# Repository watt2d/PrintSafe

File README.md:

# PrintSafe
3D filament dehumidifier based on the ESP32

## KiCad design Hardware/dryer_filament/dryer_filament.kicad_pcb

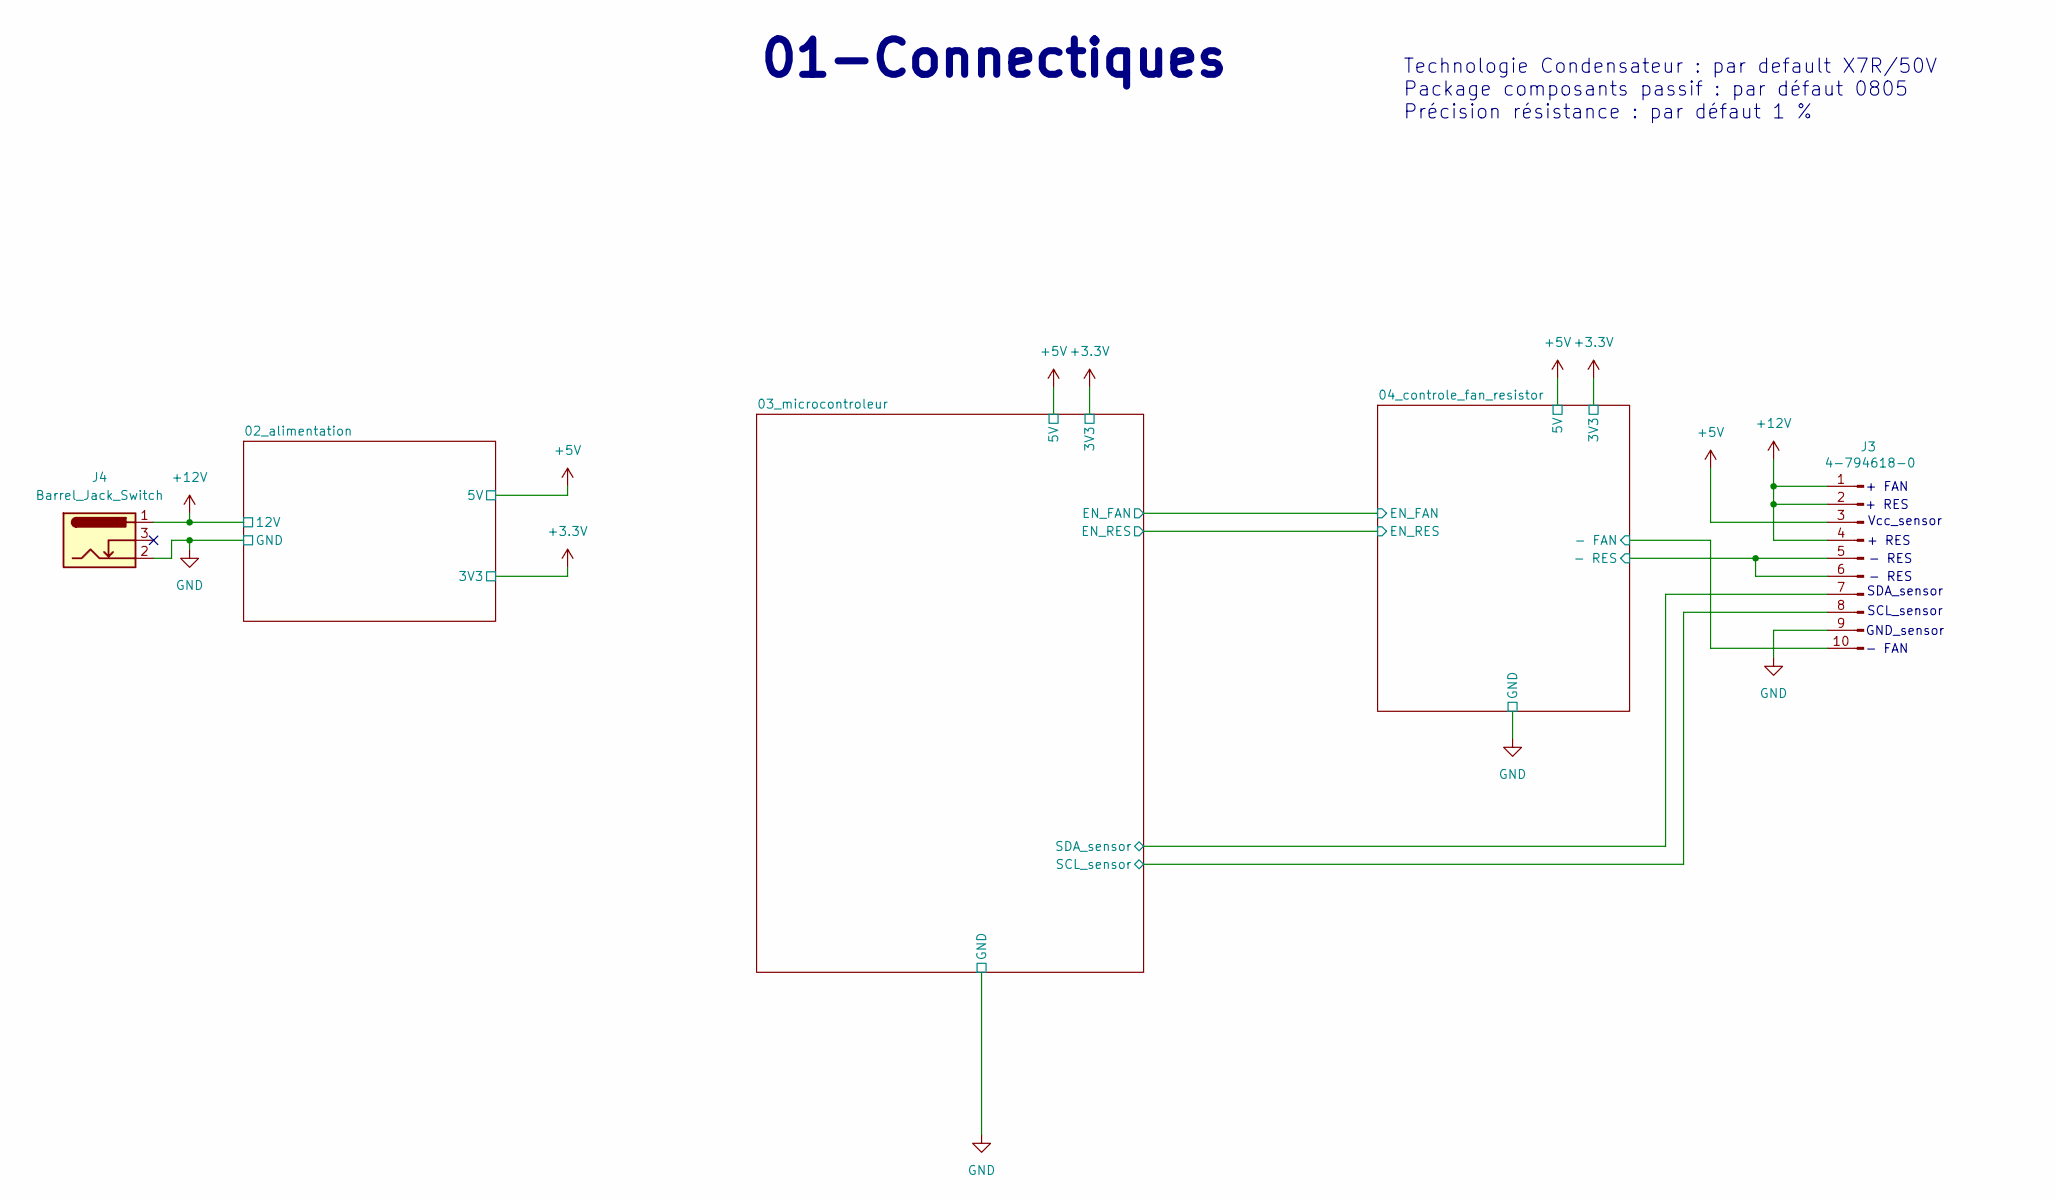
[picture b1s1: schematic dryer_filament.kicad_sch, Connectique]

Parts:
J3: 4-794618-0; 47946180
J4: Barrel_Jack_Switch; BarrelJack_CUI_PJ-102AH_Horizontal

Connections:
+5V: J3.3; also elsewhere on the board
+12V: J3.1, J3.2, J3.4, J4.1; also elsewhere on the board
/03_microcontroleur/SCL_sensor: J3.8; also elsewhere on the board
/03_microcontroleur/SDA_sensor: J3.7; also elsewhere on the board
/04_controle_fan_resistor/- FAN: J3.10; also elsewhere on the board
/04_controle_fan_resistor/- RES: J3.5, J3.6; also elsewhere on the board
GND: J3.9, J4.2; also elsewhere on the board

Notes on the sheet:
Vcc_sensor
SCL_sensor
- RES
+ RES
- FAN
+ FAN
GND_sensor
Technologie Condensateur : par default X7R/50V Package composants passif : par défaut 0805 Précision résistance : par défaut 1 %
01-Connectiques
SDA_sensor

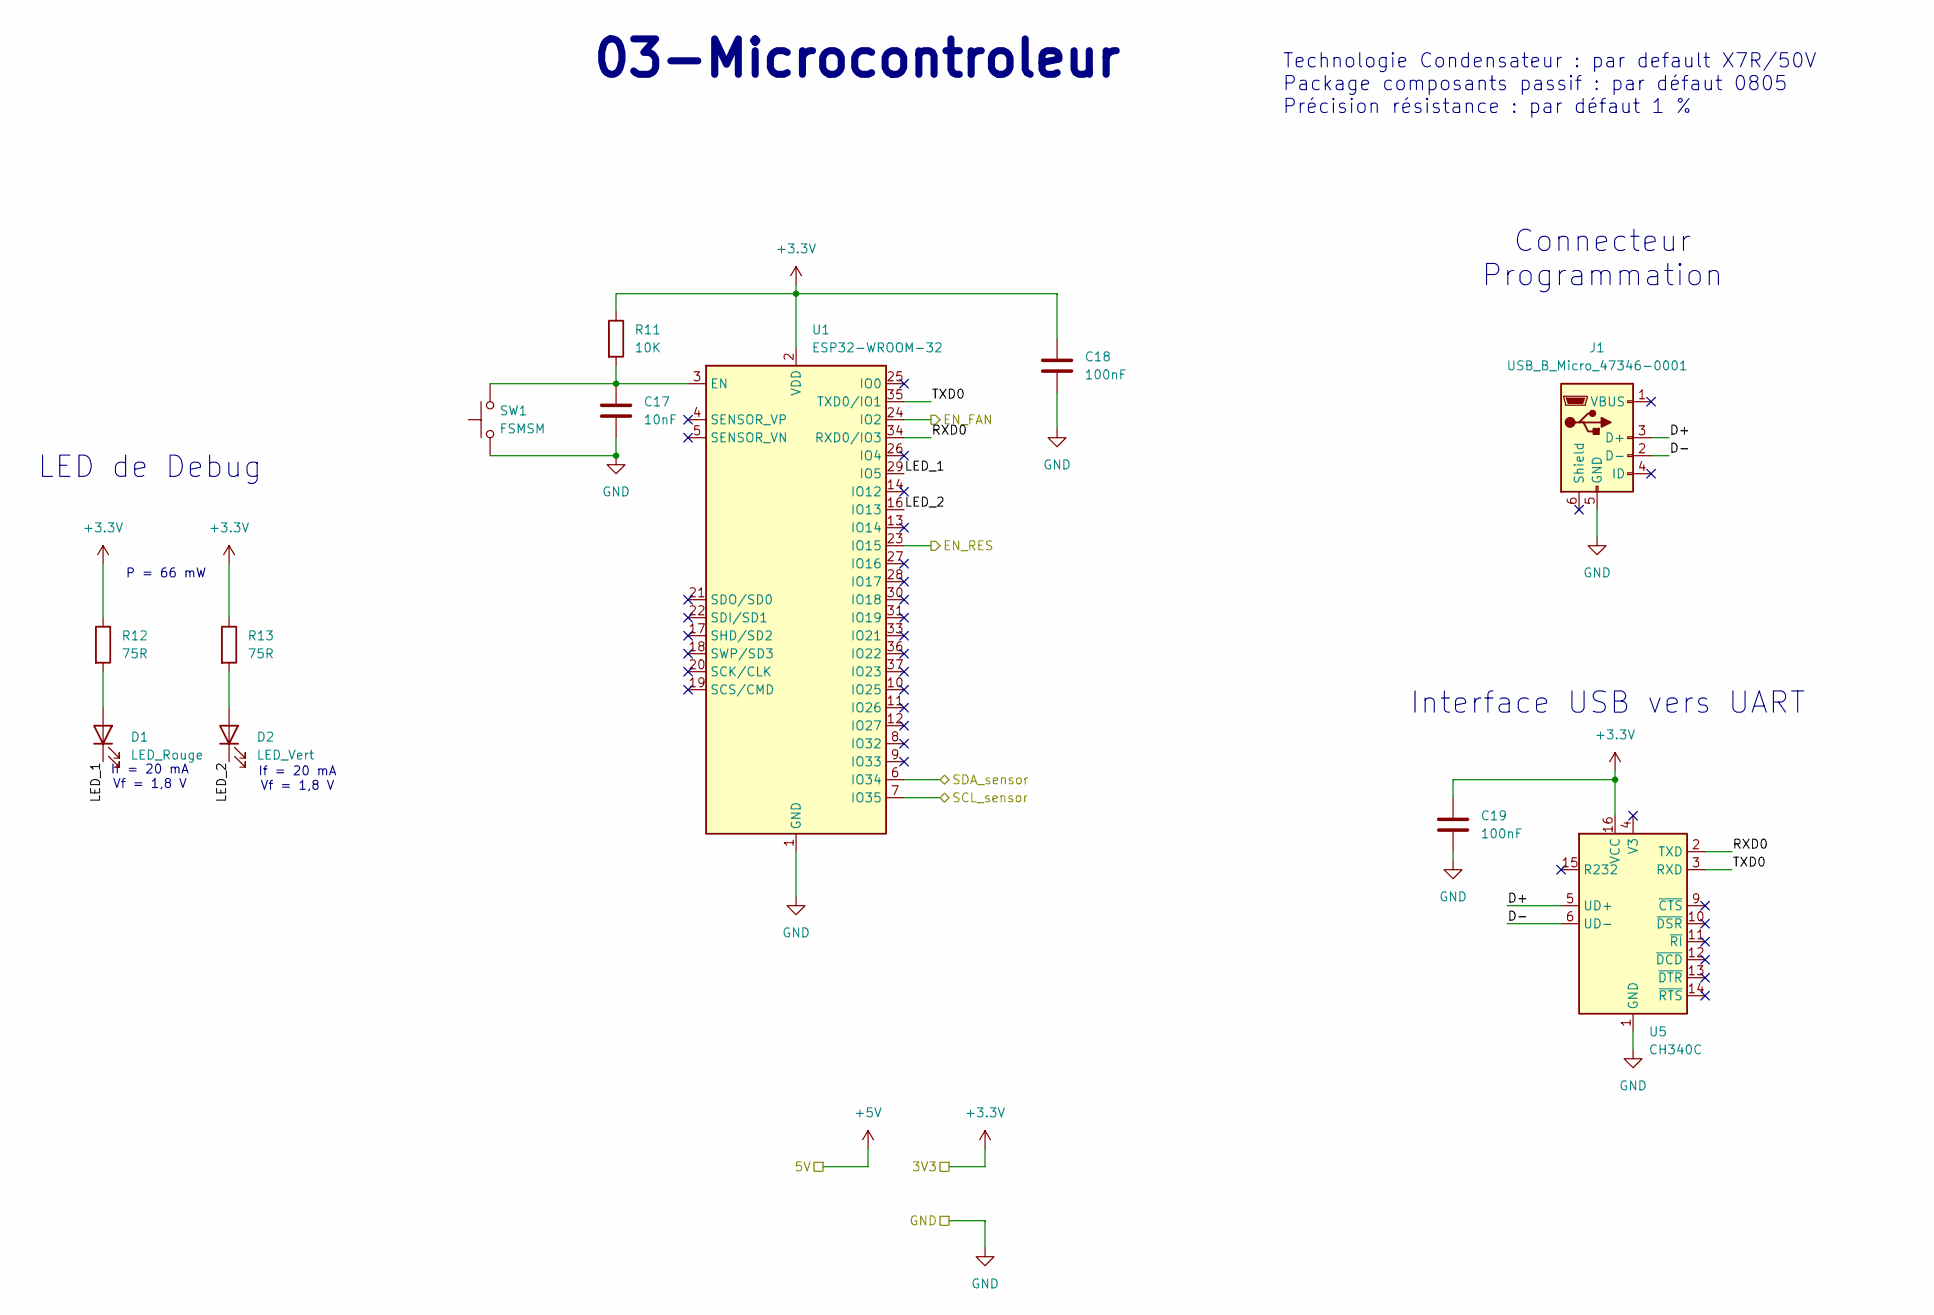
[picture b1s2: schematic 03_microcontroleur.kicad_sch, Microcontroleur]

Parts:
C17: 10nF; C_0805_2012Metric_Pad1.18x1.45mm_HandSolder
C18, C19: 100nF; C_0805_2012Metric_Pad1.18x1.45mm_HandSolder
D1: LED_Rouge; D_0805_2012Metric_Pad1.15x1.40mm_HandSolder
D2: LED_Vert; D_0805_2012Metric_Pad1.15x1.40mm_HandSolder
J1: USB_B_Micro_47346-0001; USB_Micro-B_Molex_47346-0001
R11: 10K; R_0805_2012Metric_Pad1.20x1.40mm_HandSolder
R12, R13: 75R; R_0805_2012Metric_Pad1.20x1.40mm_HandSolder
SW1: FSMSM; SW_Tactile_SPST_NO_Straight_CK_PTS636Sx25SMTRLFS
U1: ESP32-WROOM-32
U5: CH340C; SOIC-16_3.9x9.9mm_P1.27mm

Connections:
+3.3V: C18.1, C19.1, R11.1, R12.1, R13.1, U1.2 (VDD), U5.16 (VCC); also elsewhere on the board
/03_microcontroleur/D+: J1.3 (D+), U5.5 (UD+)
/03_microcontroleur/D-: J1.2 (D-), U5.6 (UD-)
/03_microcontroleur/EN_FAN: U1.24 (IO2); also elsewhere on the board
/03_microcontroleur/EN_RES: U1.23 (IO15); also elsewhere on the board
/03_microcontroleur/LED_1: D1.1 (K), U1.29 (IO5)
/03_microcontroleur/LED_2: D2.1 (K), U1.16 (IO13)
/03_microcontroleur/RXD0: U1.34 (RXD0/IO3), U5.2 (TXD)
/03_microcontroleur/SCL_sensor: U1.7 (IO35); also elsewhere on the board
/03_microcontroleur/SDA_sensor: U1.6 (IO34); also elsewhere on the board
/03_microcontroleur/TXD0: U1.35 (TXD0/IO1), U5.3 (RXD)
GND: C17.2, C18.2, C19.2, J1.5 (GND), SW1.1, U1.1 (GND), U1.15 (GND), U1.38 (GND), U1.39 (GND), U5.1 (GND); also elsewhere on the board
unnamed: D1.2 (A), R12.2
unnamed: D2.2 (A), R13.2
unnamed: C17.1, R11.2, SW1.2, U1.3 (EN)

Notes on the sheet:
Interface USB vers UART
If = 20 mA Vf = 1,8 V
Technologie Condensateur : par default X7R/50V Package composants passif : par défaut 0805 Précision résistance : par défaut 1 %
P = 66 mW
Connecteur Programmation
03-Microcontroleur
LED de Debug

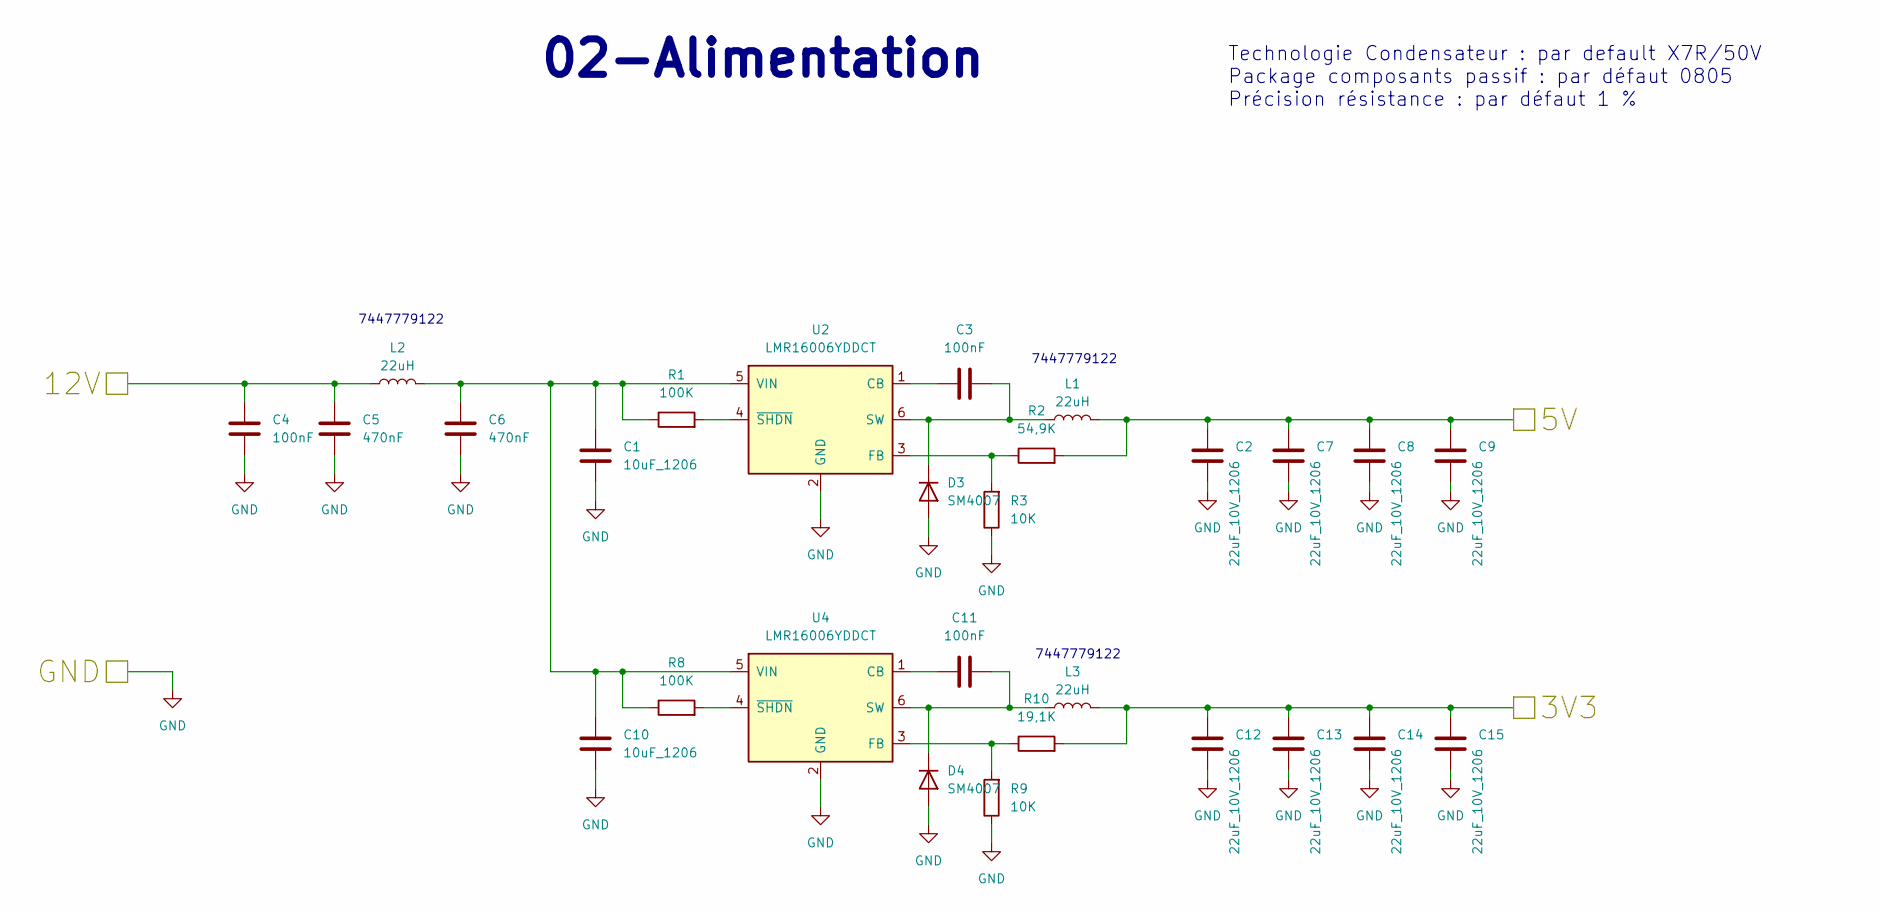
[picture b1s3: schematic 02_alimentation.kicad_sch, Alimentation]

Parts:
C1, C10: 10uF_1206; C_1206_3216Metric_Pad1.33x1.80mm_HandSolder
C2, C7, C8, C9, C12, C13, C14, C15: 22uF_10V_1206; C_1206_3216Metric_Pad1.33x1.80mm_HandSolder
C3, C4, C11: 100nF; C_0805_2012Metric_Pad1.18x1.45mm_HandSolder
C5, C6: 470nF; C_0805_2012Metric_Pad1.18x1.45mm_HandSolder
D3, D4: SM4007; D_SOD-123
L1, L2, L3: 22uH; L_Wuerth_WE-PD-Typ-M-Typ-S
R1, R8: 100K; R_0805_2012Metric_Pad1.20x1.40mm_HandSolder
R2: 54,9K; R_0805_2012Metric_Pad1.20x1.40mm_HandSolder
R3, R9: 10K; R_0805_2012Metric_Pad1.20x1.40mm_HandSolder
R10: 19,1K; R_0805_2012Metric_Pad1.20x1.40mm_HandSolder
U2, U4: LMR16006YDDCT; SOT-23-6

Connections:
+3.3V: C12.1, C13.1, C14.1, C15.1, L3.2, R10.2; also elsewhere on the board
+5V: C2.1, C7.1, C8.1, C9.1, L1.2, R2.2; also elsewhere on the board
+12V: C4.1, C5.1, L2.1; also elsewhere on the board
GND: C1.2, C2.2, C4.2, C5.2, C6.2, C7.2, C8.2, C9.2, C10.2, C12.2, C13.2, C14.2, C15.2, D3.2 (A), D4.2 (A), R3.1, R9.1, U2.2 (GND), U4.2 (GND); also elsewhere on the board
unnamed: C3.2, D3.1 (K), L1.1, U2.6 (SW)
unnamed: C11.2, D4.1 (K), L3.1, U4.6 (SW)
unnamed: C3.1, U2.1 (CB)
unnamed: R2.1, R3.2, U2.3 (FB)
unnamed: C1.1, C6.1, C10.1, L2.2, R1.1, R8.1, U2.5 (VIN), U4.5 (VIN)
unnamed: R1.2, U2.4 (~SHDN)
unnamed: C11.1, U4.1 (CB)
unnamed: R9.2, R10.1, U4.3 (FB)
unnamed: R8.2, U4.4 (~SHDN)

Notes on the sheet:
7447779122
Technologie Condensateur : par default X7R/50V Package composants passif : par défaut 0805 Précision résistance : par défaut 1 %
02-Alimentation

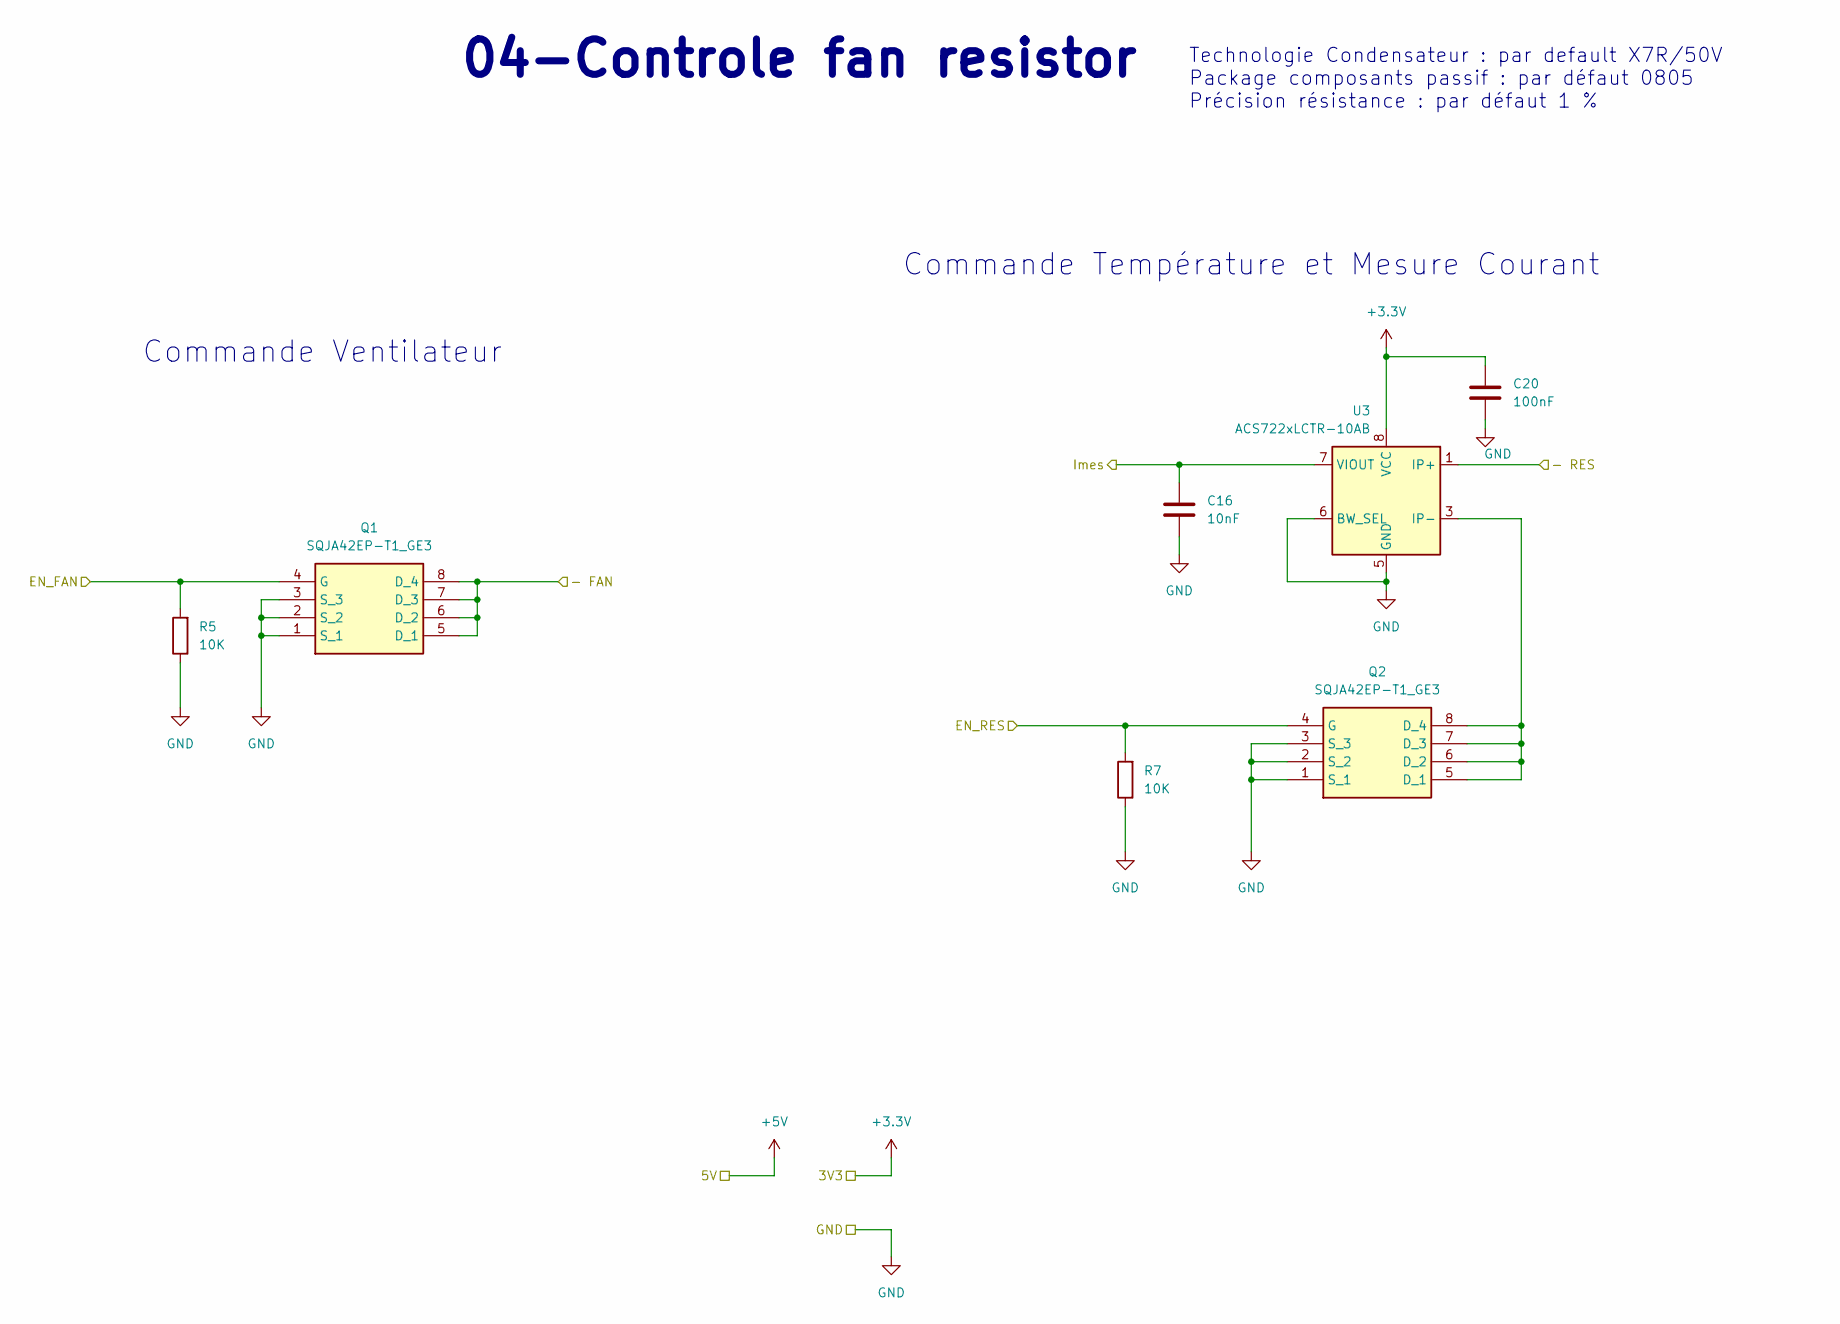
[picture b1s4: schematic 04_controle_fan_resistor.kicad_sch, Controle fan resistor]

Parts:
C16: 10nF; C_0805_2012Metric_Pad1.18x1.45mm_HandSolder
C20: 100nF; C_0805_2012Metric_Pad1.18x1.45mm_HandSolder
Q1, Q2: SQJA42EP-T1_GE3; SQJA42EPT1_GE3; Manufacturer_Part_Number SQJA42EP-T1_GE3
R5, R7: 10K; R_0805_2012Metric_Pad1.20x1.40mm_HandSolder
U3: ACS722xLCTR-10AB; SOIC-8_3.9x4.9mm_P1.27mm

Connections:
+3.3V: C20.1, U3.8 (VCC); also elsewhere on the board
/03_microcontroleur/EN_FAN: Q1.4 (G), R5.2; also elsewhere on the board
/03_microcontroleur/EN_RES: Q2.4 (G), R7.2; also elsewhere on the board
/04_controle_fan_resistor/- FAN: Q1.5 (D_1), Q1.6 (D_2), Q1.7 (D_3), Q1.8 (D_4); also elsewhere on the board
/04_controle_fan_resistor/- RES: U3.1 (IP+), U3.2 (IP+); also elsewhere on the board
/04_controle_fan_resistor/Imes: C16.1, U3.7 (VIOUT)
GND: C16.2, C20.2, Q1.1 (S_1), Q1.2 (S_2), Q1.3 (S_3), Q2.1 (S_1), Q2.2 (S_2), Q2.3 (S_3), R5.1, R7.1, U3.5 (GND), U3.6 (BW_SEL); also elsewhere on the board
unnamed: Q2.5 (D_1), Q2.6 (D_2), Q2.7 (D_3), Q2.8 (D_4), U3.3 (IP-), U3.4 (IP-)

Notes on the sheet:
Commande Température et Mesure Courant
Commande Ventilateur
04-Controle fan resistor
Technologie Condensateur : par default X7R/50V Package composants passif : par défaut 0805 Précision résistance : par défaut 1 %

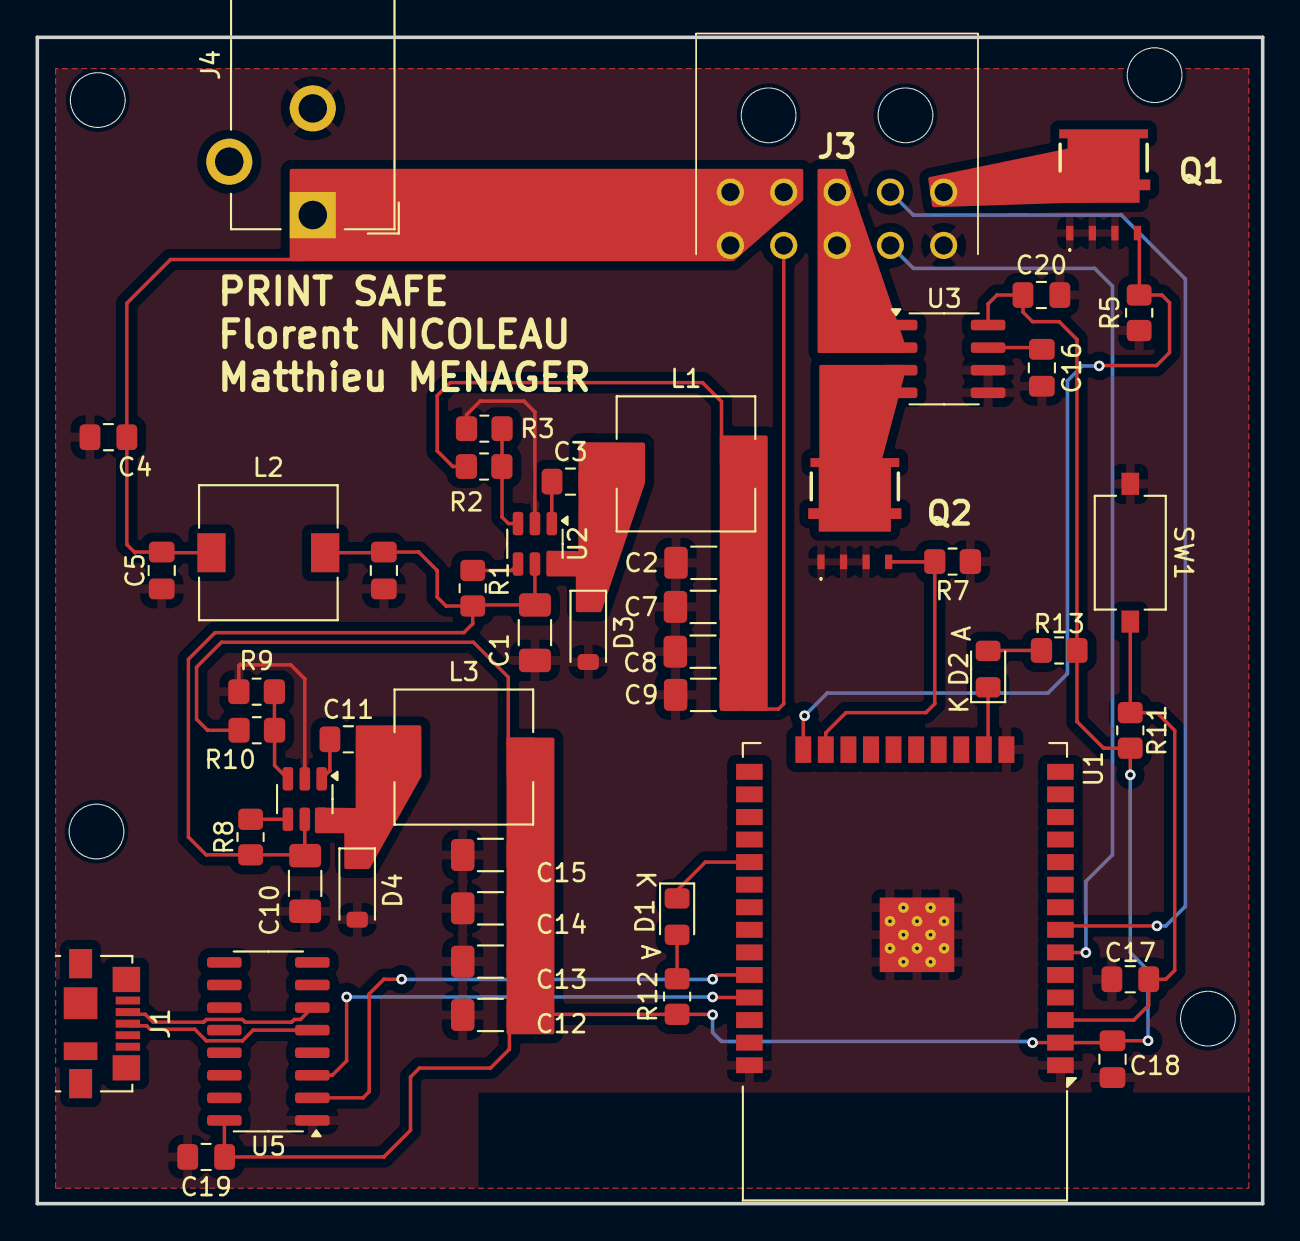
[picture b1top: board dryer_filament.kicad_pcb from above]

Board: 2 copper layers, 68.9 x 65.6 mm, 49 parts (0 on the bottom side), 30 nets.

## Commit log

2025-11-18 worked on the PWM control using mqtt TODO add I2C to receive T° and HR from sensor
2025-11-18 work the structure of the software project
2025-11-19 work on the task to send temp and hr every 5scds TODO put wifi creds in nvs iot not hardcode it
2025-11-21 work on the wifi connectivity
2025-11-21 work on the pwm and global logic
2025-11-23 work on the overall logic removed mqtt topics
2025-11-23 Added pcb files
2025-12-08 added i2C for temp and HR
2026-01-12 work on the wifi handle
2026-01-12 implementation of a control solution for the resistance
